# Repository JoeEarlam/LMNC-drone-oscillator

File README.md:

# LMNC-drone-oscillator

My own take on Look Mum No Computer's reverse avalanche oscillator, as featured in his 100 oscillator drone video. Four oscillators in a eurorack format, with a buffered output.

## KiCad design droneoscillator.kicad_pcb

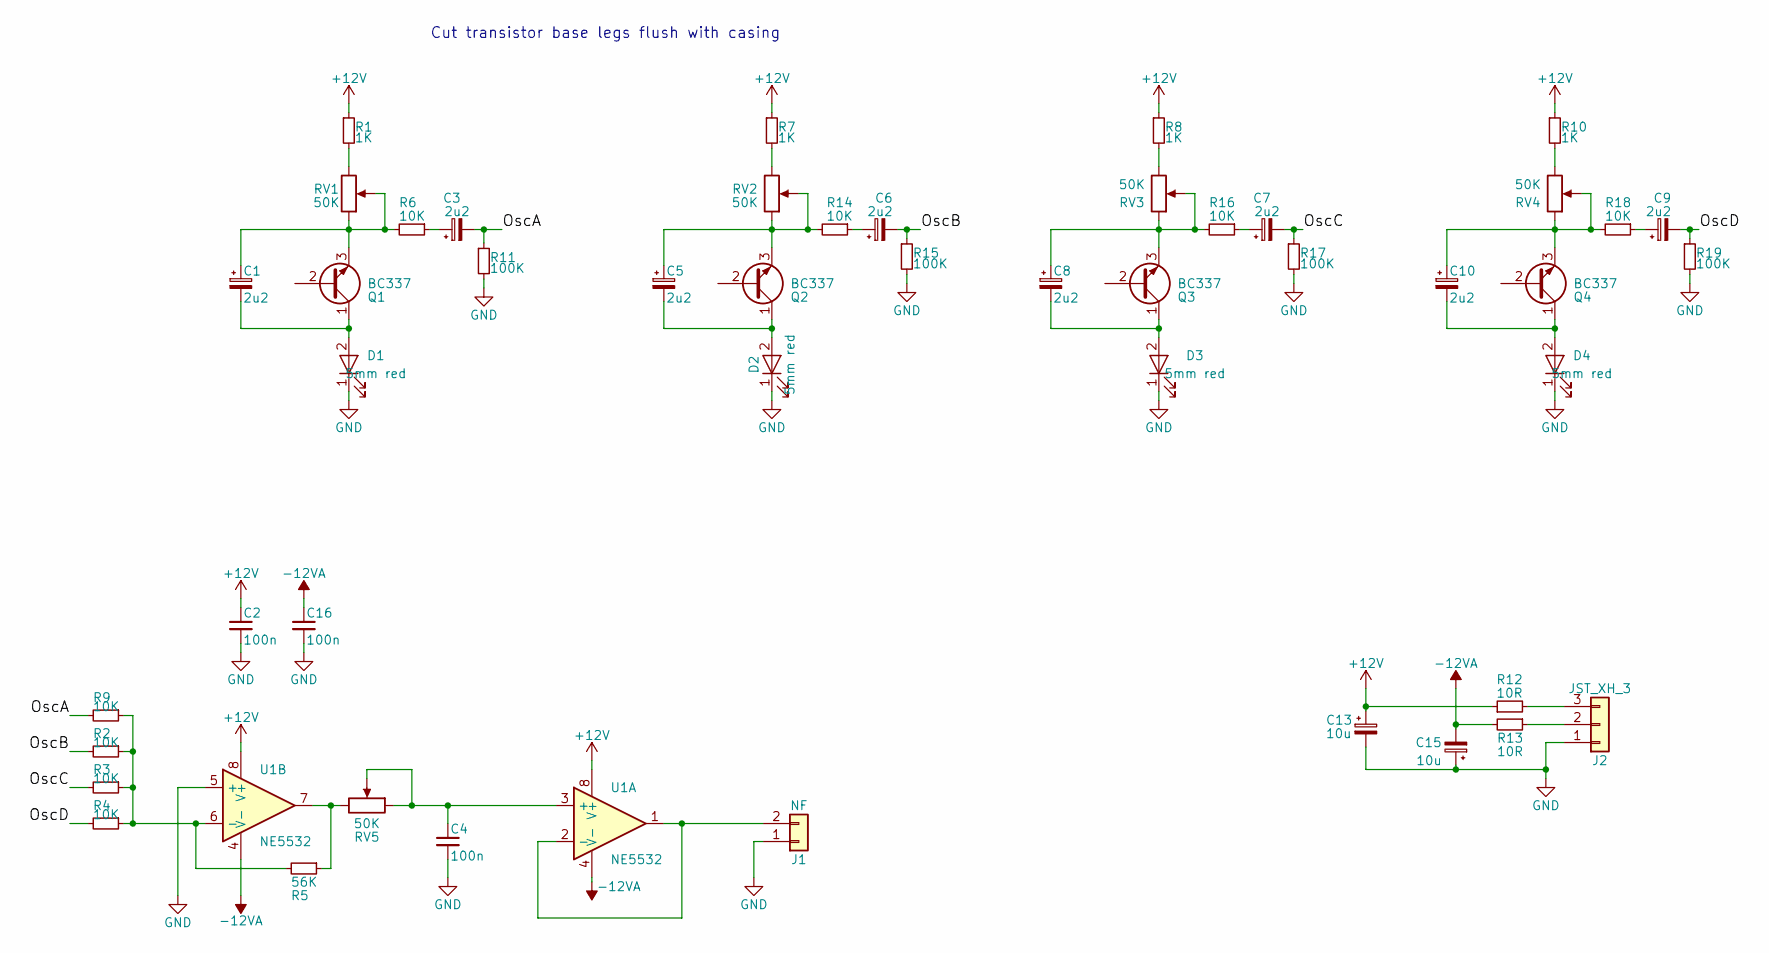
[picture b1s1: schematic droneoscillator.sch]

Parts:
C1, C3, C5, C6, C7, C8, C9, C10: 2u2; CP_Radial_D4.0mm_P2.00mm
C2, C4, C16: 100n; C_Disc_D4.3mm_W1.9mm_P5.00mm
C13, C15: 10u; CP_Radial_D4.0mm_P2.00mm
D1, D2, D3, D4: 5mm red; LED_D5.0mm_Horizontal_O1.27mm_Z3.0mm
J1: NF; JST_XH_B02B-XH-A_1x02_P2.50mm_Vertical
J2: JST_XH_3; JST_XH_B03B-XH-A_1x03_P2.50mm_Vertical
Q1, Q2, Q3, Q4: BC337; TO-92_Inline_Wide
R1, R7, R8, R10: 1K; R_Axial_DIN0204_L3.6mm_D1.6mm_P7.62mm_Horizontal
R2, R3, R4, R6, R9, R14, R16, R18: 10K; R_Axial_DIN0204_L3.6mm_D1.6mm_P7.62mm_Horizontal
R5: 56K; R_Axial_DIN0204_L3.6mm_D1.6mm_P7.62mm_Horizontal
R11, R15, R17, R19: 100K; R_Axial_DIN0204_L3.6mm_D1.6mm_P7.62mm_Horizontal
R12, R13: 10R; R_Axial_DIN0204_L3.6mm_D1.6mm_P7.62mm_Horizontal
RV1, RV2, RV3, RV4, RV5: 50K; Potentiometer_Alps_RK097_Single_Horizontal
U1: NE5532; DIP-8_W7.62mm_Socket_LongPads

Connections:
+12V: C2.1, C13.1, R1.1, R7.1, R8.1, R10.1, R12.1, U1.8 (V+)
-12VA: C15.2, C16.1, R13.2, U1.4 (V-)
/OscA: C3.2, R9.2, R11.1
/OscB: C6.2, R2.2, R15.1
/OscC: C7.2, R3.2, R17.1
/OscD: C9.2, R4.2, R19.1
GND: C2.2, C4.2, C13.2, C15.1, C16.2, D1.1 (K), D2.1 (K), D3.1 (K), D4.1 (K), J1.1, J2.1, R11.2, R15.2, R17.2, R19.2, U1.5 (+)
unnamed: C1.1, Q1.3 (E), R6.2, RV1.1, RV1.2
unnamed: C1.2, D1.2 (A), Q1.1 (C)
unnamed: C3.1, R6.1
unnamed: C4.1, RV5.1, RV5.2, U1.3 (+)
unnamed: C5.1, Q2.3 (E), R14.2, RV2.1, RV2.2
unnamed: C5.2, D2.2 (A), Q2.1 (C)
unnamed: C6.1, R14.1
unnamed: C7.1, R16.1
unnamed: C8.1, Q3.3 (E), R16.2, RV3.1, RV3.2
unnamed: C8.2, D3.2 (A), Q3.1 (C)
unnamed: C9.1, R18.1
unnamed: C10.1, Q4.3 (E), R18.2, RV4.1, RV4.2
unnamed: C10.2, D4.2 (A), Q4.1 (C)
unnamed: J1.2, U1.1, U1.2 (-)
unnamed: J2.2, R13.1
unnamed: J2.3, R12.2
unnamed: R1.2, RV1.3
unnamed: R2.1, R3.1, R4.1, R5.2, R9.1, U1.6 (-)
unnamed: R5.1, RV5.3, U1.7
unnamed: R7.2, RV2.3
unnamed: R8.2, RV3.3
unnamed: R10.2, RV4.3

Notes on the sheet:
Cut transistor base legs flush with casing

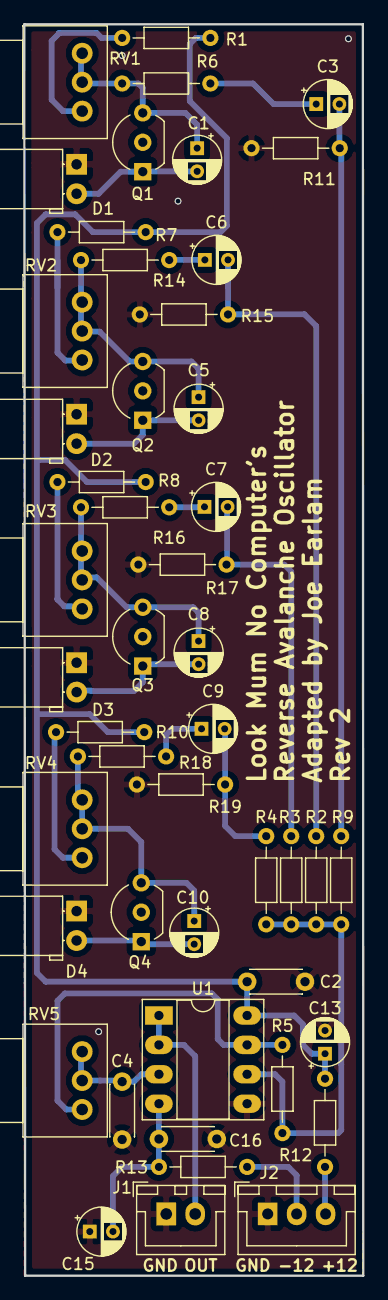
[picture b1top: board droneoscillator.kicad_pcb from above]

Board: 2 copper layers, 29.3 x 108.1 mm, 48 parts (0 on the bottom side), 29 nets.

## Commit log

2018-11-15 Fixed typo in readme, added pdf schematic
2019-01-04 Bug fixes after first prototype build
2019-01-07 update after prototype build, new PCB layout
2019-01-07 schematic bugfix, minor changes to PCB
2019-01-07 silkscreen bugfix
2019-01-08 cleaned up cruft
2019-01-09 change lowest oscillation frequency to 20Hz, fix low output fromixer, minor PCB fixes
2019-01-09 added git ignore
2019-01-10 added front panel, adjusted PCB slightly to improve front panel real estate
2019-01-16 Added front panel
2019-01-16 update front panel
2019-01-21 Minor schematic changes after prototype build, cleaned up PCB design
2019-01-24 updated gitignore
2019-01-31 added input filtering to power supply
2019-01-31 pcb and schematic tweaks
2019-02-01 changed PCB dimensions to fit wider range of racks
2019-02-02 small tweaks, ready for sending to production
2019-02-02 updated front panel hole dimensions
2019-02-07 tag for release to production
2019-02-10 as sent to production
2019-02-18 front panel changes
2019-02-19 updated front panel
2019-02-19 Minor BOM adjustments
2019-03-05 updated BOM + component notes
